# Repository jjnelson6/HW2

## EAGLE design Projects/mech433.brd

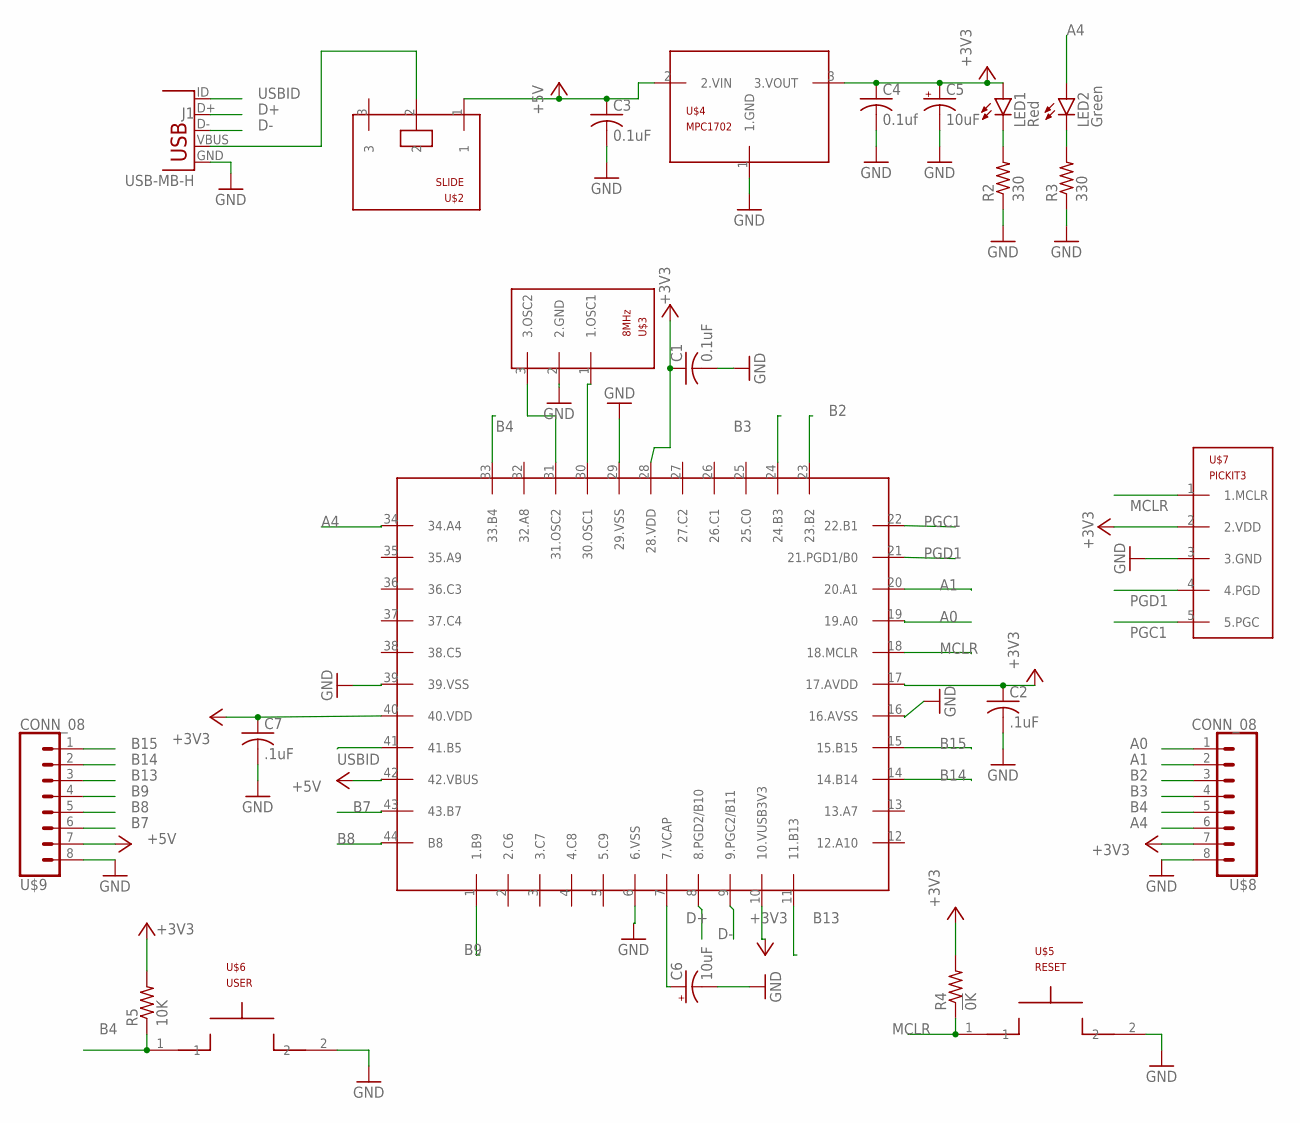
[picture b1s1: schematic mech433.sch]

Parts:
C1, C3: 0.1uF; C025-025X050
C2, C7: .1uF; C025-025X050
C4: 0.1uf; C025-025X050
C5, C6: 10uF; B45181B
J1: USB-MB-H
LED1: Red; LED3MM
LED2: Green; LED3MM
R2, R3: 330; 0207/10
R4: !0K; 0207/10
R5: 10K; 0207/10
U$1: PIC32MX250F256D; TQFP44
U$2: SLIDE
U$3: 8MHz; OSC
U$4: MPC1702; TO92
U$5: RESET; PB
U$6: USER; PB
U$7: PICKIT3; 1X05
U$8, U$9: CONN_08; 1X08

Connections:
+3V3: C1.1, C2.1, C4.1, C5.+, C7.1, LED1.A, R4.2, R5.2, U$1.10 (10.VUSB3V3), U$1.17 (17.AVDD), U$1.28 (28.VDD), U$1.40 (40.VDD), U$4.3 (3.VOUT), U$7.2 (2.VDD), U$8.7
+5V: C3.1, U$1.42 (42.VBUS), U$2.1, U$4.2 (2.VIN), U$9.7
A0: U$1.19 (19.A0), U$8.1
A1: U$1.20 (20.A1), U$8.2
A4: LED2.A, U$1.34 (34.A4), U$8.6
B2: U$1.23 (23.B2), U$8.3
B3: U$1.24 (24.B3), U$8.4
B4: R5.1, U$1.33 (33.B4), U$6.1, U$8.5
B7: U$1.43 (43.B7), U$9.6
B8: U$1.44 (B8), U$9.5
B9: U$1.1 (1.B9), U$9.4
B13: U$1.11 (11.B13), U$9.3
B14: U$1.14 (14.B14), U$9.2
B15: U$1.15 (15.B15), U$9.1
D+: J1.D+, U$1.8 (8.PGD2/B10)
D-: J1.D-, U$1.9 (9.PGC2/B11)
GND: C1.2, C2.2, C3.2, C4.2, C5.-, C6.-, C7.2, J1.GND, R2.1, R3.1, U$1.6 (6.VSS), U$1.16 (16.AVSS), U$1.29 (29.VSS), U$1.39 (39.VSS), U$3.2 (2.GND), U$4.1 (1.GND), U$5.2, U$6.2, U$7.3 (3.GND), U$8.8, U$9.8
MCLR: R4.1, U$1.18 (18.MCLR), U$5.1, U$7.1 (1.MCLR)
unnamed: LED1.K (C), R2.2
unnamed: LED2.K (C), R3.2
unnamed: U$1.30 (30.OSC1), U$3.1 (1.OSC1)
unnamed: U$1.31 (31.OSC2), U$3.3 (3.OSC2)
unnamed: C6.+, U$1.7 (7.VCAP)
PGC1: U$1.22 (22.B1), U$7.5 (5.PGC)
PGD1: U$1.21 (21.PGD1/B0), U$7.4 (4.PGD)
USBID: J1.ID, U$1.41 (41.B5)
VBUS: J1.VBUS, U$2.2

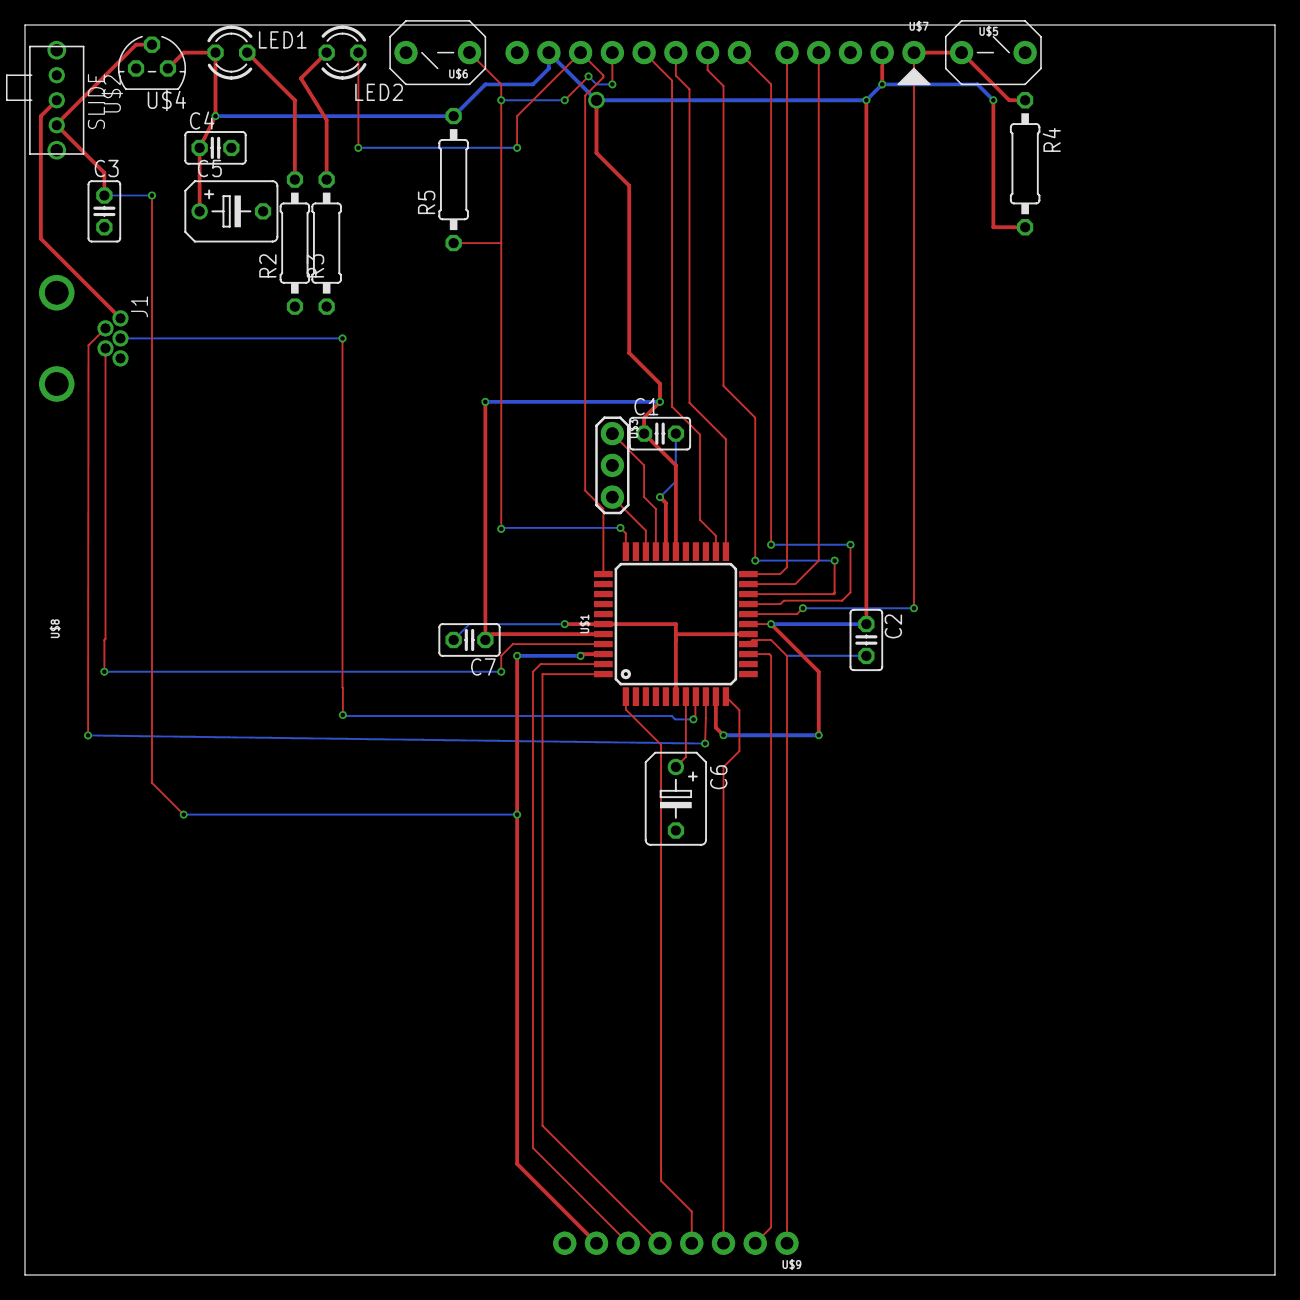
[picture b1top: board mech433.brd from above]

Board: 2 copper layers, 100.0 x 100.0 mm, 23 parts (0 on the bottom side), 27 nets.

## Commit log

2019-04-08 Made USB,Slide,OSC,Connectors
2019-04-10 made PIC
2019-04-11 schematic update
2019-04-13 Finished Schematic
2019-05-02 Making Board
2019-05-03 Connected 3.3 Volts
2019-05-04 Connected All of the Power and GND
2019-05-04 Completed_all_basic_connections
2019-05-04 Error_Checked
